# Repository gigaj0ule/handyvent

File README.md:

See this page for further details: https://civilpedia.org/p/?pid=338

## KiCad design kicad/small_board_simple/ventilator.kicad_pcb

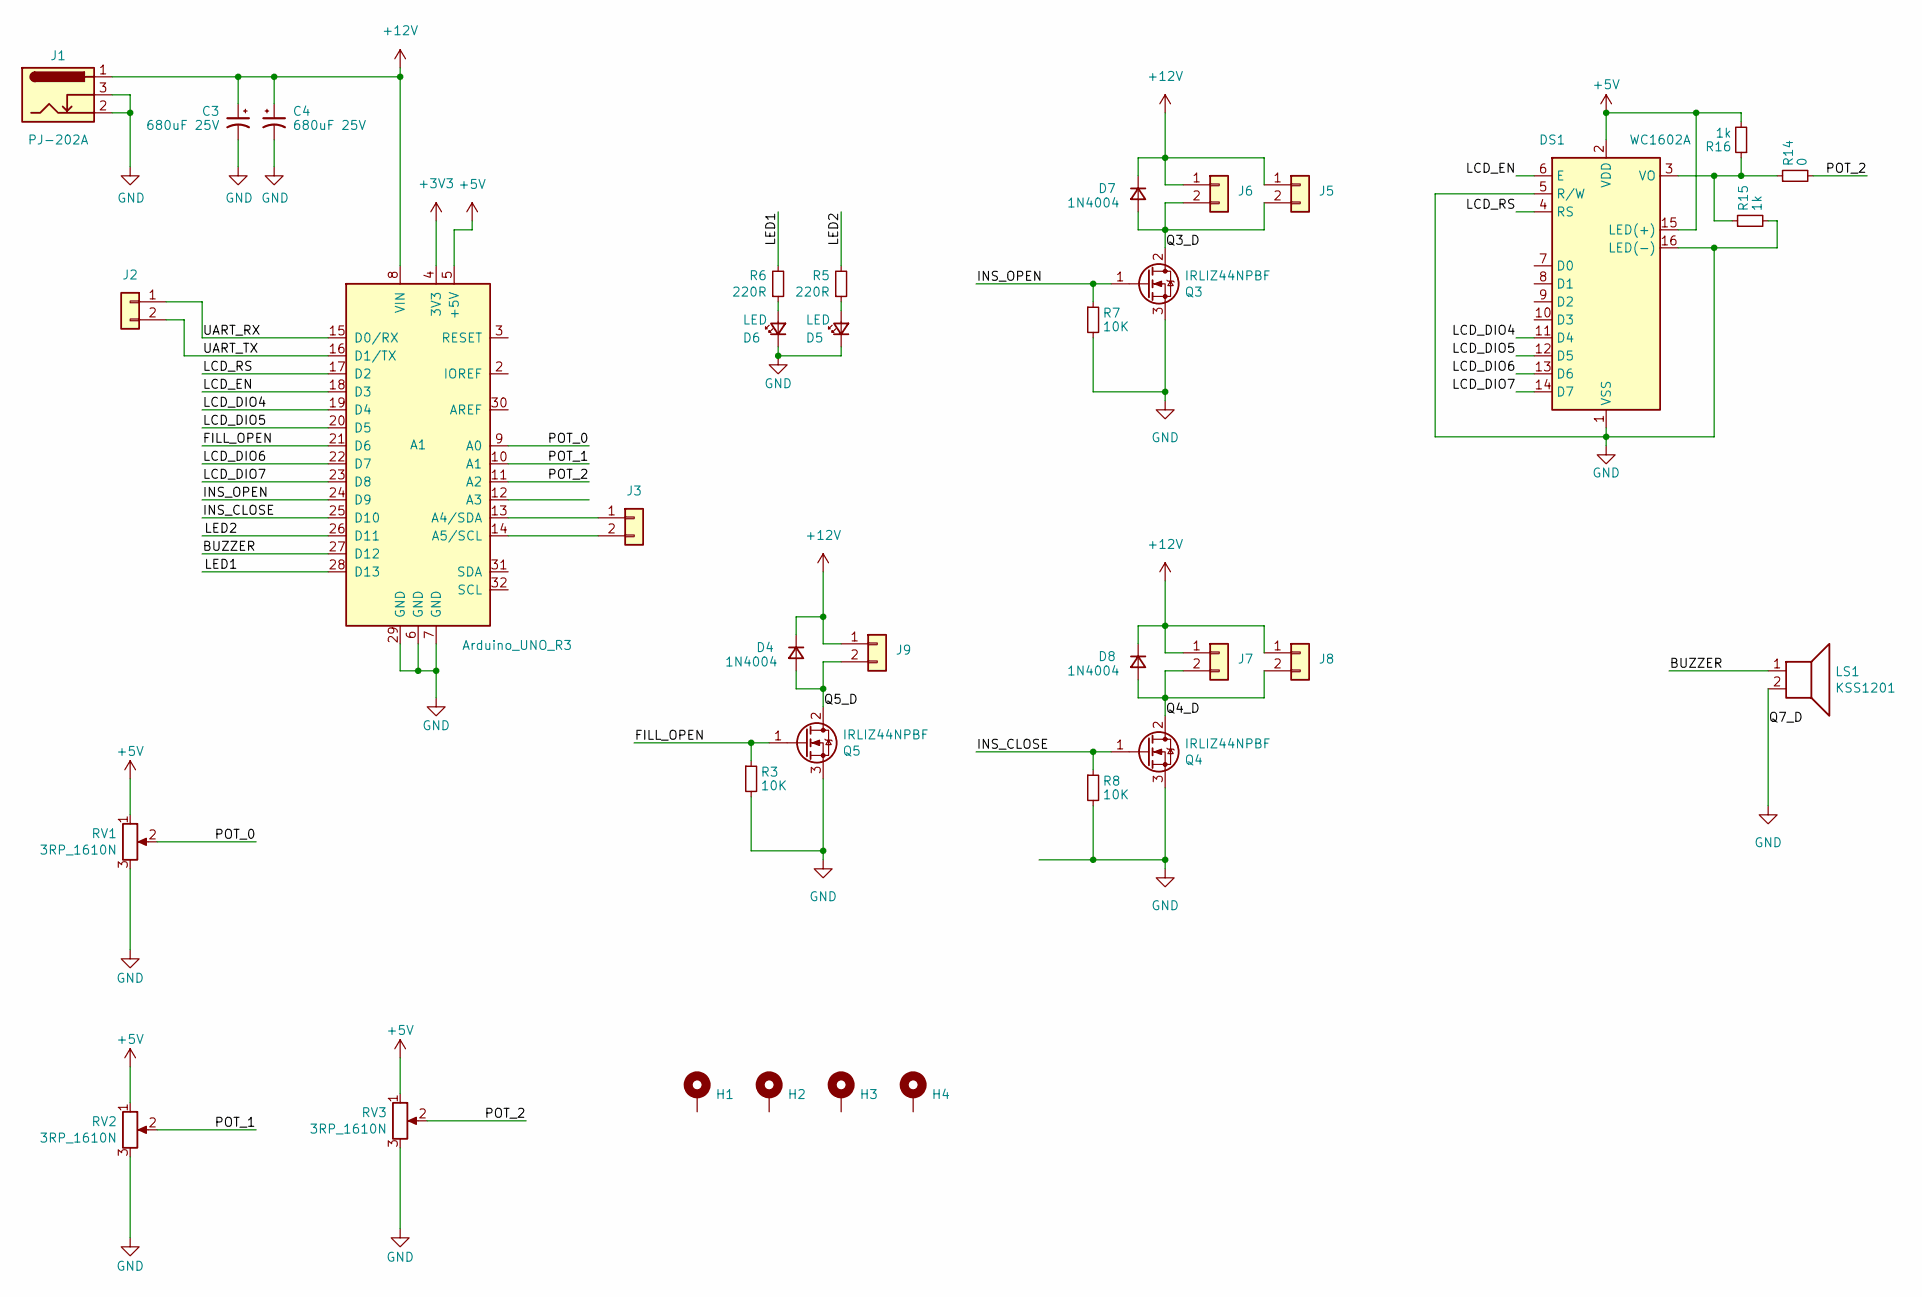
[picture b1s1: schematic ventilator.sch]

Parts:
A1: Arduino_UNO_R3; Arduino_UNO_R3_large_pads
C3, C4: 680uF 25V; CP_Radial_D10.0mm_P5.00mm
D4, D7, D8: 1N4004; D_DO-41_SOD81_P7.62mm_Horizontal
D5, D6: LED; LED_D5.0mm
DS1: WC1602A
H1, H2, H3, H4: MountingHole_Pad; MountingHole_2.2mm_M2
J1: PJ-202A; BarrelJack_Horizontal
J2, J3: Conn_01x02; PinHeader_1x02_P2.54mm_Vertical
J5, J6, J7, J8, J9: Conn_01x02; TerminalBlock_Phoenix_MKDS-1,5-2-5.08_1x02_P5.08mm_Horizont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
LS1: KSS1201; Buzzer_TDK_PS1240P02BT_D12.2mm_H6.5mm
Q3, Q4, Q5: IRLIZ44NPBF; TO-220-3_Vertical
R3, R7, R8: 10K; R_Axial_DIN0207_L6.3mm_D2.5mm_P7.62mm_Horizontal
R5, R6: 220R; R_Axial_DIN0207_L6.3mm_D2.5mm_P7.62mm_Horizontal
R14: 0; R_Axial_DIN0207_L6.3mm_D2.5mm_P7.62mm_Horizontal
R15, R16: 1k; R_Axial_DIN0207_L6.3mm_D2.5mm_P7.62mm_Horizontal
RV1, RV2, RV3: 3RP_1610N; Potentiometer_Piher_T-16H_Single_Horizontal

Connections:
+3V3: A1.4 (3V3)
+5V: A1.5 (+5V), DS1.2 (VDD), DS1.15 (LED(+)), R16.2, RV1.1, RV2.1, RV3.1
+12V: A1.8 (VIN), C3.1, C4.1, D4.1 (K), D7.1 (K), D8.1 (K), J1.1, J5.1, J6.1, J7.1, J8.1, J9.1
/BUZZER: A1.27 (D12), LS1.1
/FILL_OPEN: A1.21 (D6), Q5.1 (G), R3.1
/INS_CLOSE: A1.25 (D10), Q4.1 (G), R8.1
/INS_OPEN: A1.24 (D9), Q3.1 (G), R7.1
/LCD_DIO4: A1.19 (D4), DS1.11 (D4)
/LCD_DIO5: A1.20 (D5), DS1.12 (D5)
/LCD_DIO6: A1.22 (D7), DS1.13 (D6)
/LCD_DIO7: A1.23 (D8), DS1.14 (D7)
/LCD_EN: A1.18 (D3), DS1.6 (E)
/LCD_RS: A1.17 (D2), DS1.4 (RS)
/LED1: A1.28 (D13), R6.2
/LED2: A1.26 (D11), R5.2
/POT_0: A1.9 (A0), RV1.2
/POT_1: A1.10 (A1), RV2.2
/POT_2: A1.11 (A2), R14.2, RV3.2
/Q3_D: D7.2 (A), J5.2, J6.2, Q3.2 (D)
/Q4_D: D8.2 (A), J7.2, J8.2, Q4.2 (D)
/Q5_D: D4.2 (A), J9.2, Q5.2 (D)
/UART_RX: A1.15 (D0/RX), J2.1
/UART_TX: A1.16 (D1/TX), J2.2
GND: A1.6 (GND), A1.7 (GND), A1.29 (GND), C3.2, C4.2, D5.1 (K), D6.1 (K), DS1.1 (VSS), DS1.5 (R/W), DS1.16 (LED(-)), J1.2, J1.3, LS1.2, Q3.3 (S), Q4.3 (S), Q5.3 (S), R3.2, R7.2, R8.2, R15.2, RV1.3, RV2.3, RV3.3
unnamed: A1.13 (A4/SDA), J3.1
unnamed: A1.14 (A5/SCL), J3.2
unnamed: D5.2 (A), R5.1
unnamed: D6.2 (A), R6.1
unnamed: DS1.3 (VO), R14.1, R15.1, R16.1

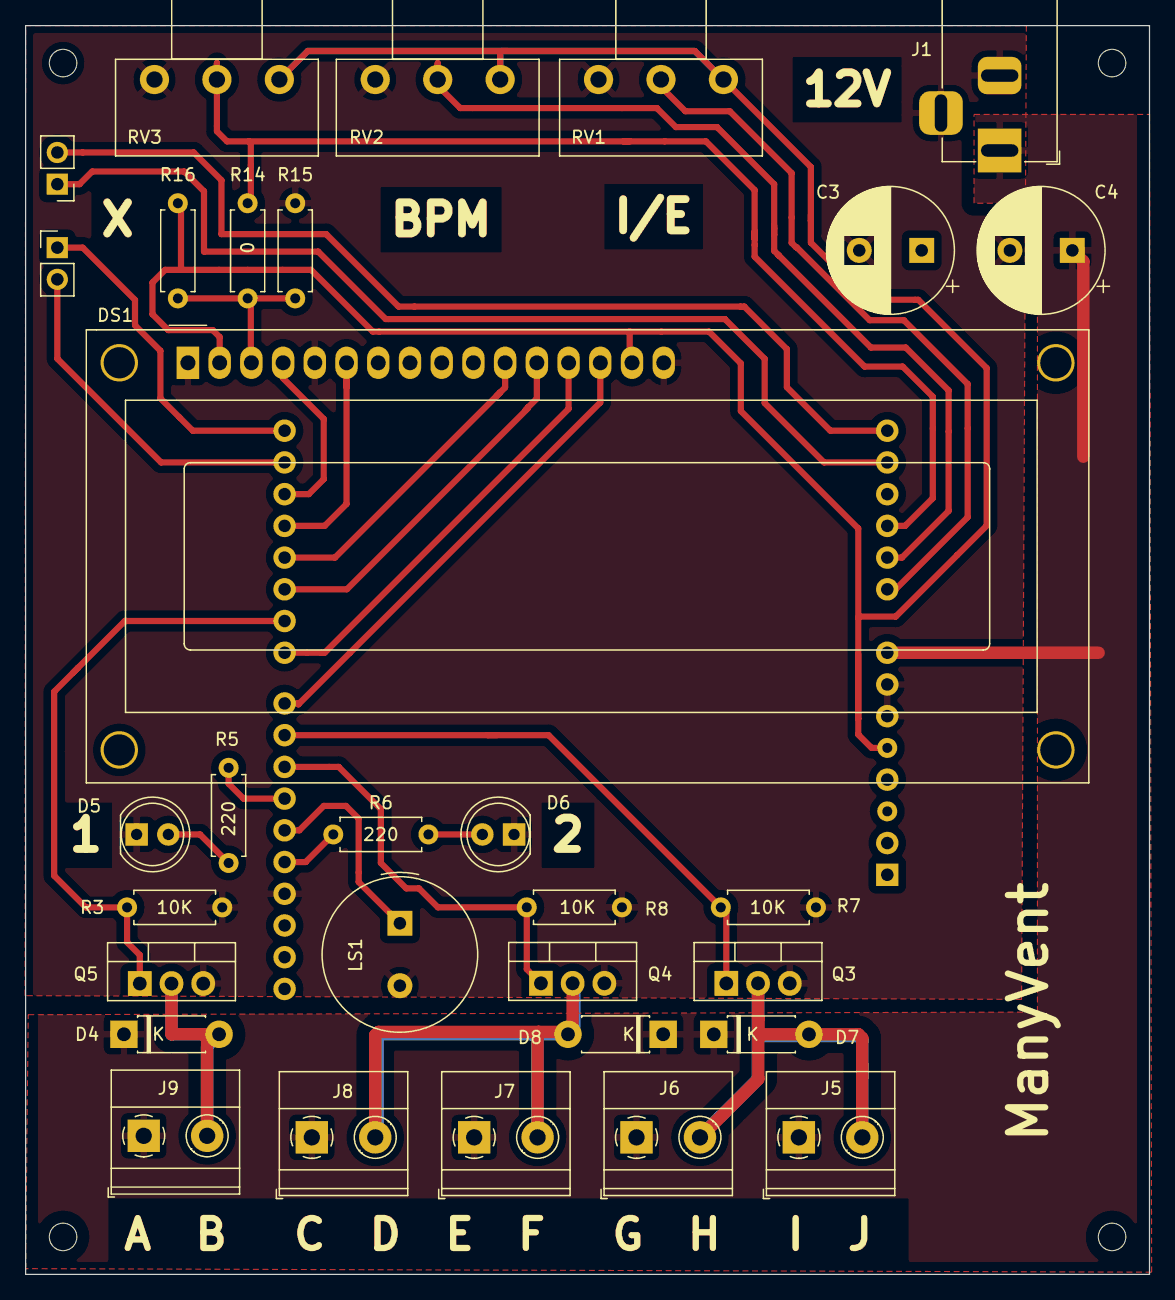
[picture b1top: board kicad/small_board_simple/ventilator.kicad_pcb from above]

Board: 2 copper layers, 90.0 x 100.0 mm, 36 parts (1 on the bottom side), 28 nets.

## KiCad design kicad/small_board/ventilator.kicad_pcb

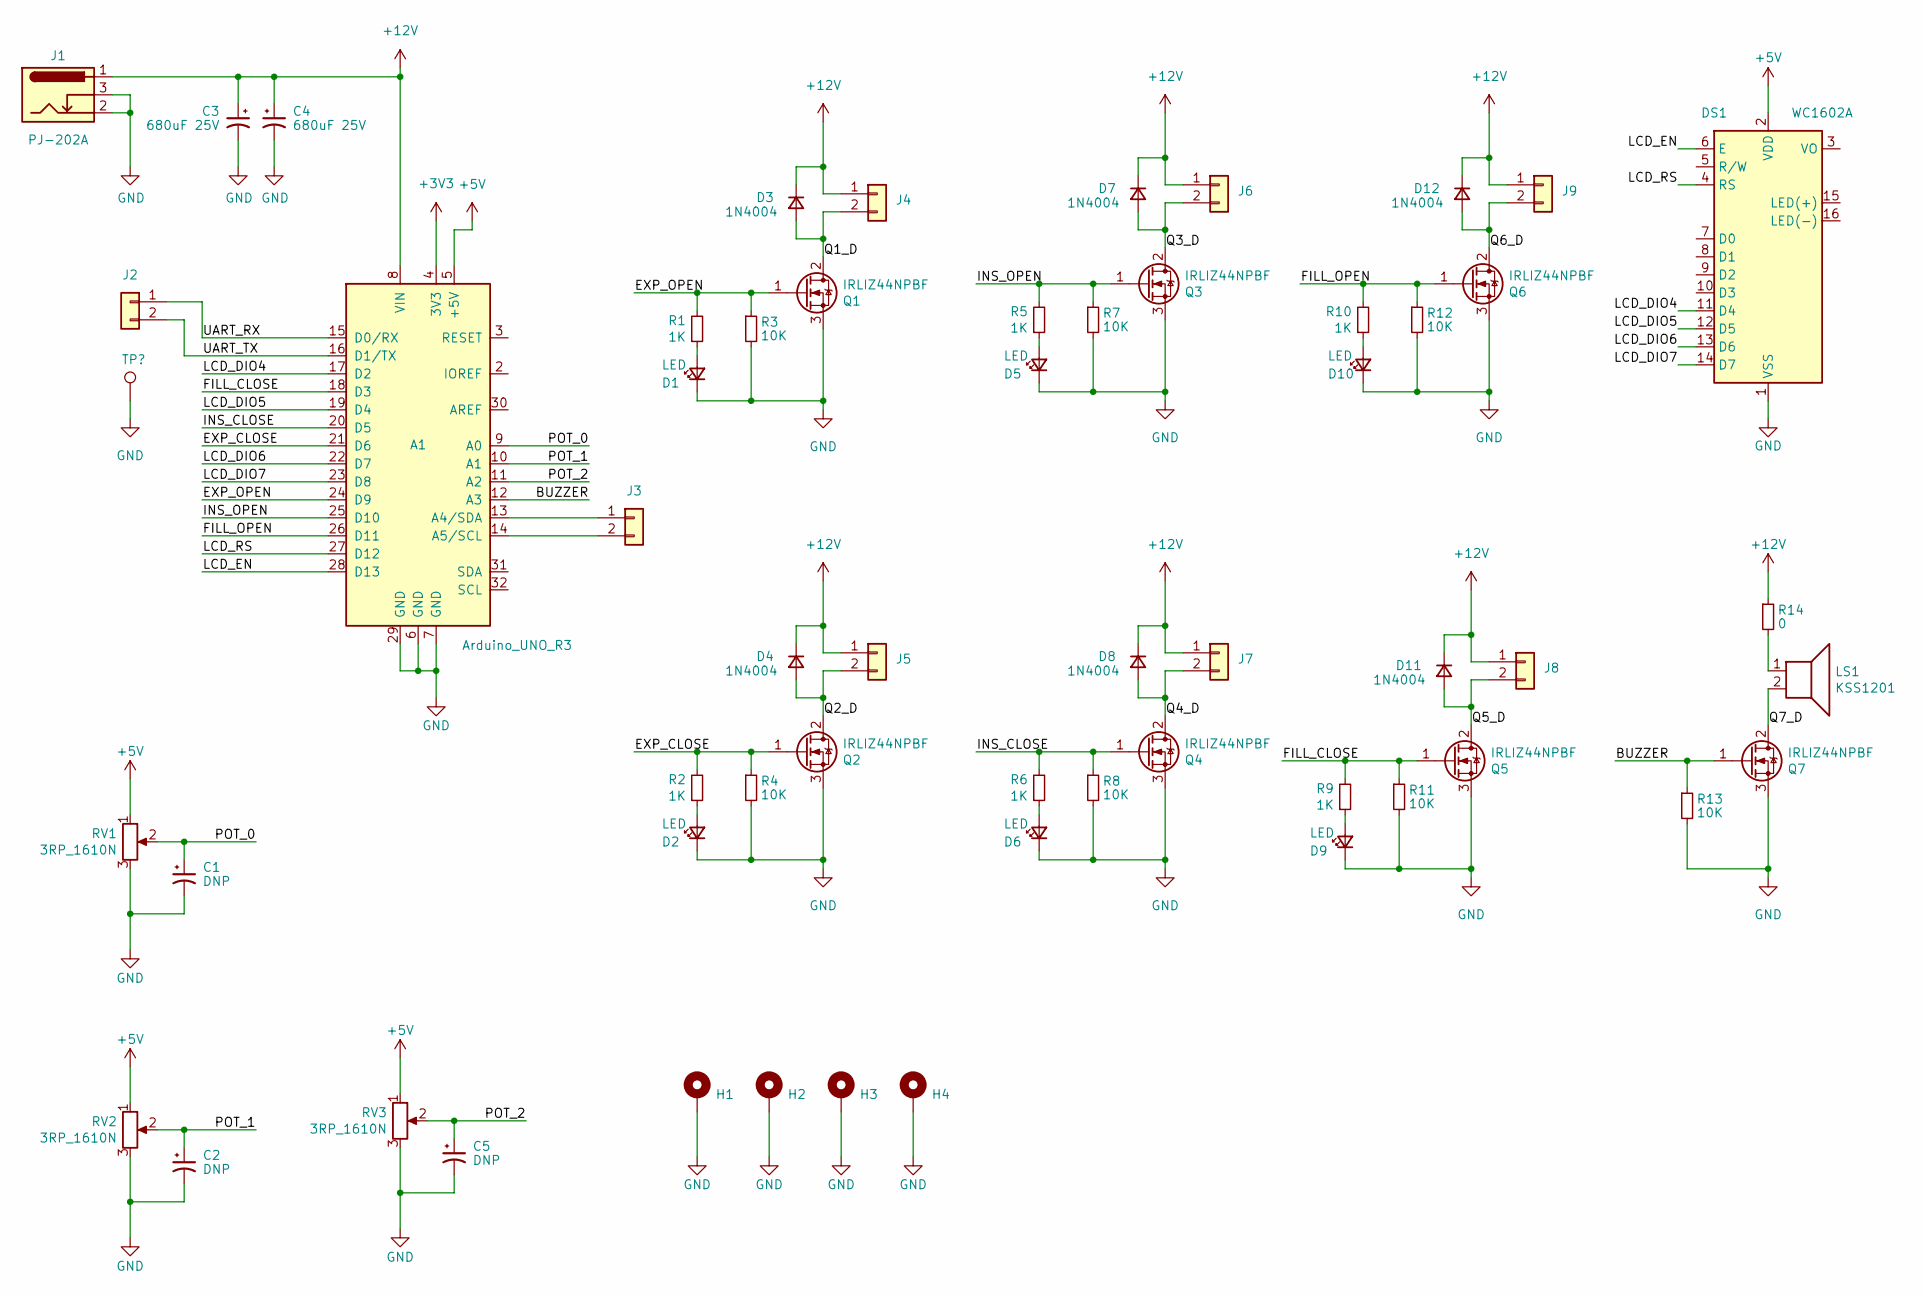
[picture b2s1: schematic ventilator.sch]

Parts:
A1: Arduino_UNO_R3
C1, C2, C5: DNP; CP_Radial_D6.3mm_P2.50mm
C3, C4: 680uF 25V; CP_Radial_D10.0mm_P5.00mm
D1, D2, D5, D6, D9, D10: LED; LED_D5.0mm
D3, D4, D7, D8, D11, D12: 1N4004; D_DO-41_SOD81_P7.62mm_Horizontal
DS1: WC1602A
H1, H2, H3, H4: MountingHole_Pad; MountingHole_2.2mm_M2
J1: PJ-202A; BarrelJack_Horizontal
J2, J3: Conn_01x02; PinHeader_1x02_P2.54mm_Vertical
J4, J5, J6, J7, J8, J9: Conn_01x02; TerminalBlock_Phoenix_MKDS-1,5-2-5.08_1x02_P5.08mm_Horizont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
LS1: KSS1201; Buzzer_TDK_PS1240P02BT_D12.2mm_H6.5mm
Q1, Q2, Q3, Q4, Q5, Q6, Q7: IRLIZ44NPBF; TO-220-3_Vertical
R1, R2, R5, R6, R9, R10: 1K; R_Axial_DIN0207_L6.3mm_D2.5mm_P7.62mm_Horizontal
R3, R4, R7, R8, R11, R12, R13: 10K; R_Axial_DIN0207_L6.3mm_D2.5mm_P7.62mm_Horizontal
R14: 0; R_Axial_DIN0207_L6.3mm_D2.5mm_P7.62mm_Horizontal
RV1, RV2, RV3: 3RP_1610N; Potentiometer_Piher_T-16H_Single_Horizontal

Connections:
+3V3: A1.4 (3V3)
+5V: A1.5 (+5V), DS1.2 (VDD), RV1.1, RV2.1, RV3.1
+12V: A1.8 (VIN), C3.1, C4.1, D3.1 (K), D4.1 (K), D7.1 (K), D8.1 (K), D11.1 (K), D12.1 (K), J1.1, J4.1, J5.1, J6.1, J7.1, J8.1, J9.1, R14.1
/BUZZER: A1.12 (A3), Q7.1 (G), R13.1
/EXP_CLOSE: A1.21 (D6), Q2.1 (G), R2.2, R4.1
/EXP_OPEN: A1.24 (D9), Q1.1 (G), R1.2, R3.1
/FILL_CLOSE: A1.18 (D3), Q5.1 (G), R9.2, R11.1
/FILL_OPEN: A1.26 (D11), Q6.1 (G), R10.2, R12.1
/INS_CLOSE: A1.20 (D5), Q4.1 (G), R6.2, R8.1
/INS_OPEN: A1.25 (D10), Q3.1 (G), R5.2, R7.1
/LCD_DIO4: A1.17 (D2), DS1.11 (D4)
/LCD_DIO5: A1.19 (D4), DS1.12 (D5)
/LCD_DIO6: A1.22 (D7), DS1.13 (D6)
/LCD_DIO7: A1.23 (D8), DS1.14 (D7)
/LCD_EN: A1.28 (D13), DS1.6 (E)
/LCD_RS: A1.27 (D12), DS1.4 (RS)
/POT_0: A1.9 (A0), C1.1, RV1.2
/POT_1: A1.10 (A1), C2.1, RV2.2
/POT_2: A1.11 (A2), C5.1, RV3.2
/Q1_D: D3.2 (A), J4.2, Q1.2 (D)
/Q2_D: D4.2 (A), J5.2, Q2.2 (D)
/Q3_D: D7.2 (A), J6.2, Q3.2 (D)
/Q4_D: D8.2 (A), J7.2, Q4.2 (D)
/Q5_D: D11.2 (A), J8.2, Q5.2 (D)
/Q6_D: D12.2 (A), J9.2, Q6.2 (D)
/Q7_D: LS1.2, Q7.2 (D)
/UART_RX: A1.15 (D0/RX), J2.1
/UART_TX: A1.16 (D1/TX), J2.2
GND: A1.6 (GND), A1.7 (GND), A1.29 (GND), C1.2, C2.2, C3.2, C4.2, C5.2, D1.1 (K), D2.1 (K), D5.1 (K), D6.1 (K), D9.1 (K), D10.1 (K), DS1.1 (VSS), H1.1, H2.1, H3.1, H4.1, J1.2, J1.3, Q1.3 (S), Q2.3 (S), Q3.3 (S), Q4.3 (S), Q5.3 (S), Q6.3 (S), Q7.3 (S), R3.2, R4.2, R7.2, R8.2, R11.2, R12.2, R13.2, RV1.3, RV2.3, RV3.3; also elsewhere on the board
unnamed: A1.13 (A4/SDA), J3.1
unnamed: A1.14 (A5/SCL), J3.2
unnamed: D1.2 (A), R1.1
unnamed: D2.2 (A), R2.1
unnamed: D5.2 (A), R5.1
unnamed: D6.2 (A), R6.1
unnamed: D9.2 (A), R9.1
unnamed: D10.2 (A), R10.1
unnamed: LS1.1, R14.2

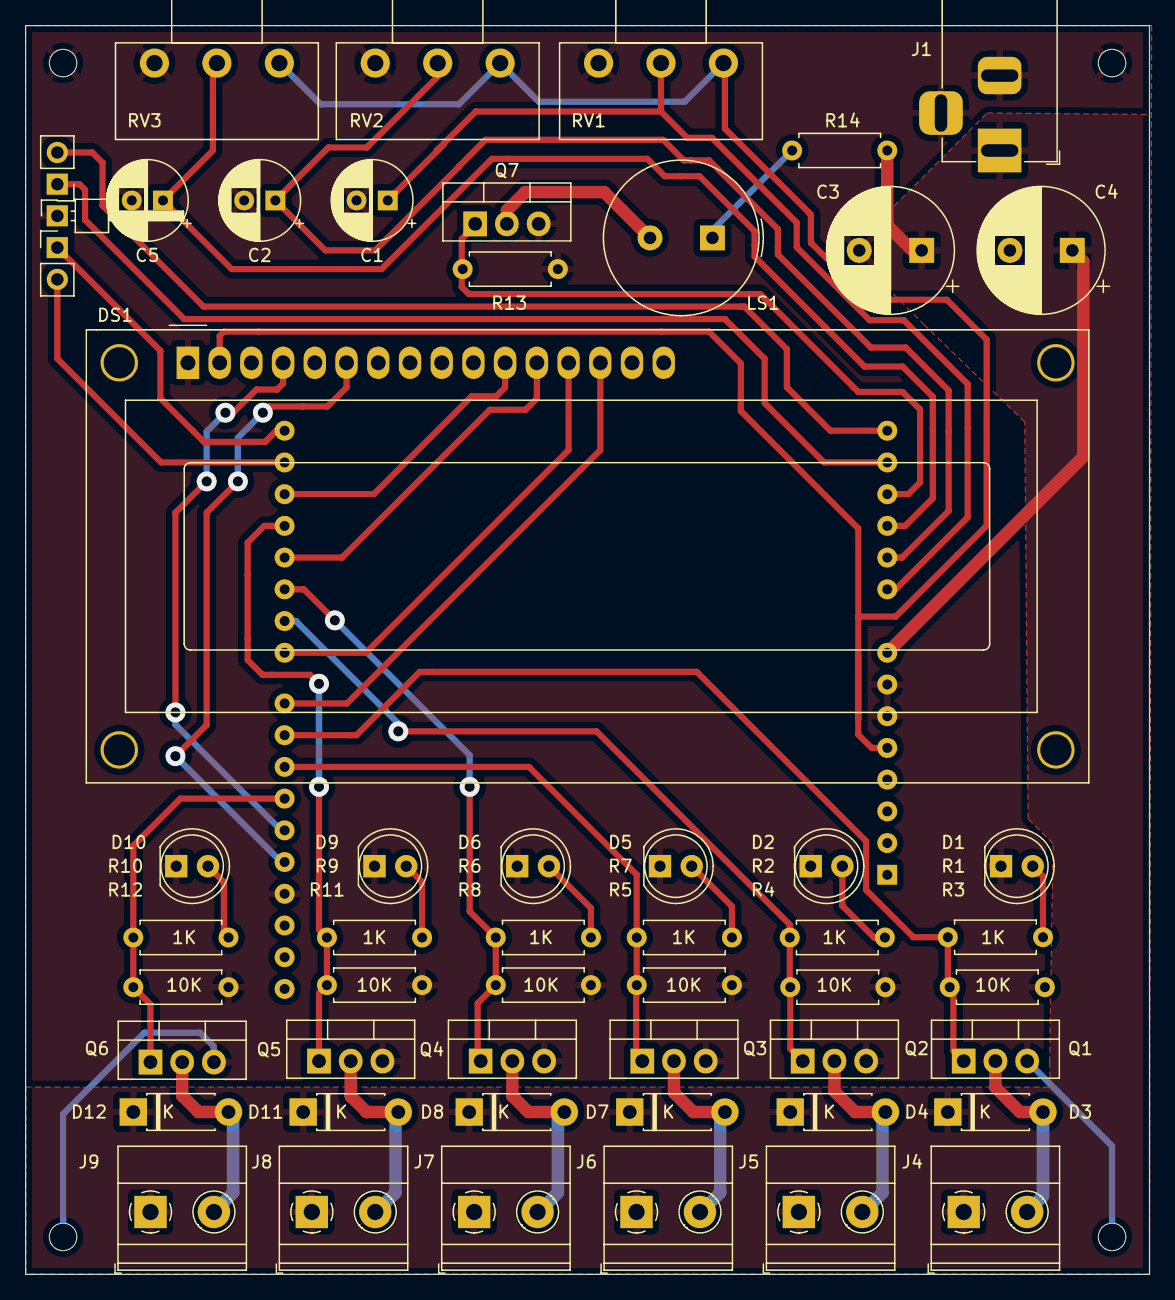
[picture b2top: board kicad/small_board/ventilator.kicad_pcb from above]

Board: 2 copper layers, 90.0 x 100.0 mm, 58 parts (1 on the bottom side), 37 nets.

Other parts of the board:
TP1: TestPoint; PinHeader_1x01_P2.54mm_Horizontal

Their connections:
GND: TP1.1; also elsewhere on the board

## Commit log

2020-03-21 it compiles on the first try
2020-03-21 Add README.md
2020-03-22 is it working?
2020-03-22 oops, cycle_time not time_start_ventilate
2020-03-22 fix knob math and version string
2020-03-22 switch time constants to 32 bit
2020-03-22 make time between inhale and exhale valves
2020-03-22 change wiring to put valves on PWM pins
2020-03-22 the analogWrite is commented out so this should change nothing
2020-03-22 change knob behavior
2020-03-22 fix constant types
2020-03-23 Add new directory
2020-03-23 added bom, schematics files and footprints
2020-03-25 adds completed kicad schematic
2020-03-25 adds pdf of kicad schematic
2020-03-26 modifies schematic with new pin mapping
2020-03-26 finishes basic kicad board layout
2020-03-27 change software for two 3-wire air valves
2020-03-28 splits the kicad design into large and small boards
2020-03-28 decent placement for kicad small board
2020-03-28 finishes layout of small kicad PCB
2020-03-28 touches up small kicad pcb layout
2020-03-28 adds copper gerber layers for small board
2020-03-28 fixes transistor order, adds ground test point
2020-03-28 finish silkscreen for small kicad board
2020-03-28 clearances
2020-03-28 gerbers
2020-03-30 simple_pcb
2020-03-30 enlarges arduino footprint pads:
2020-03-30 updates GERBERs
2020-03-30 update.ino
2020-03-30 make cycles_per_min a float
2020-03-30 Adds Knob class.
    Factors out scaling computations, and makes the checkKnob
    function more understandable.
2020-03-30 tvgijnfkmefr
2020-04-09 Add new file
2020-04-09 Update License
